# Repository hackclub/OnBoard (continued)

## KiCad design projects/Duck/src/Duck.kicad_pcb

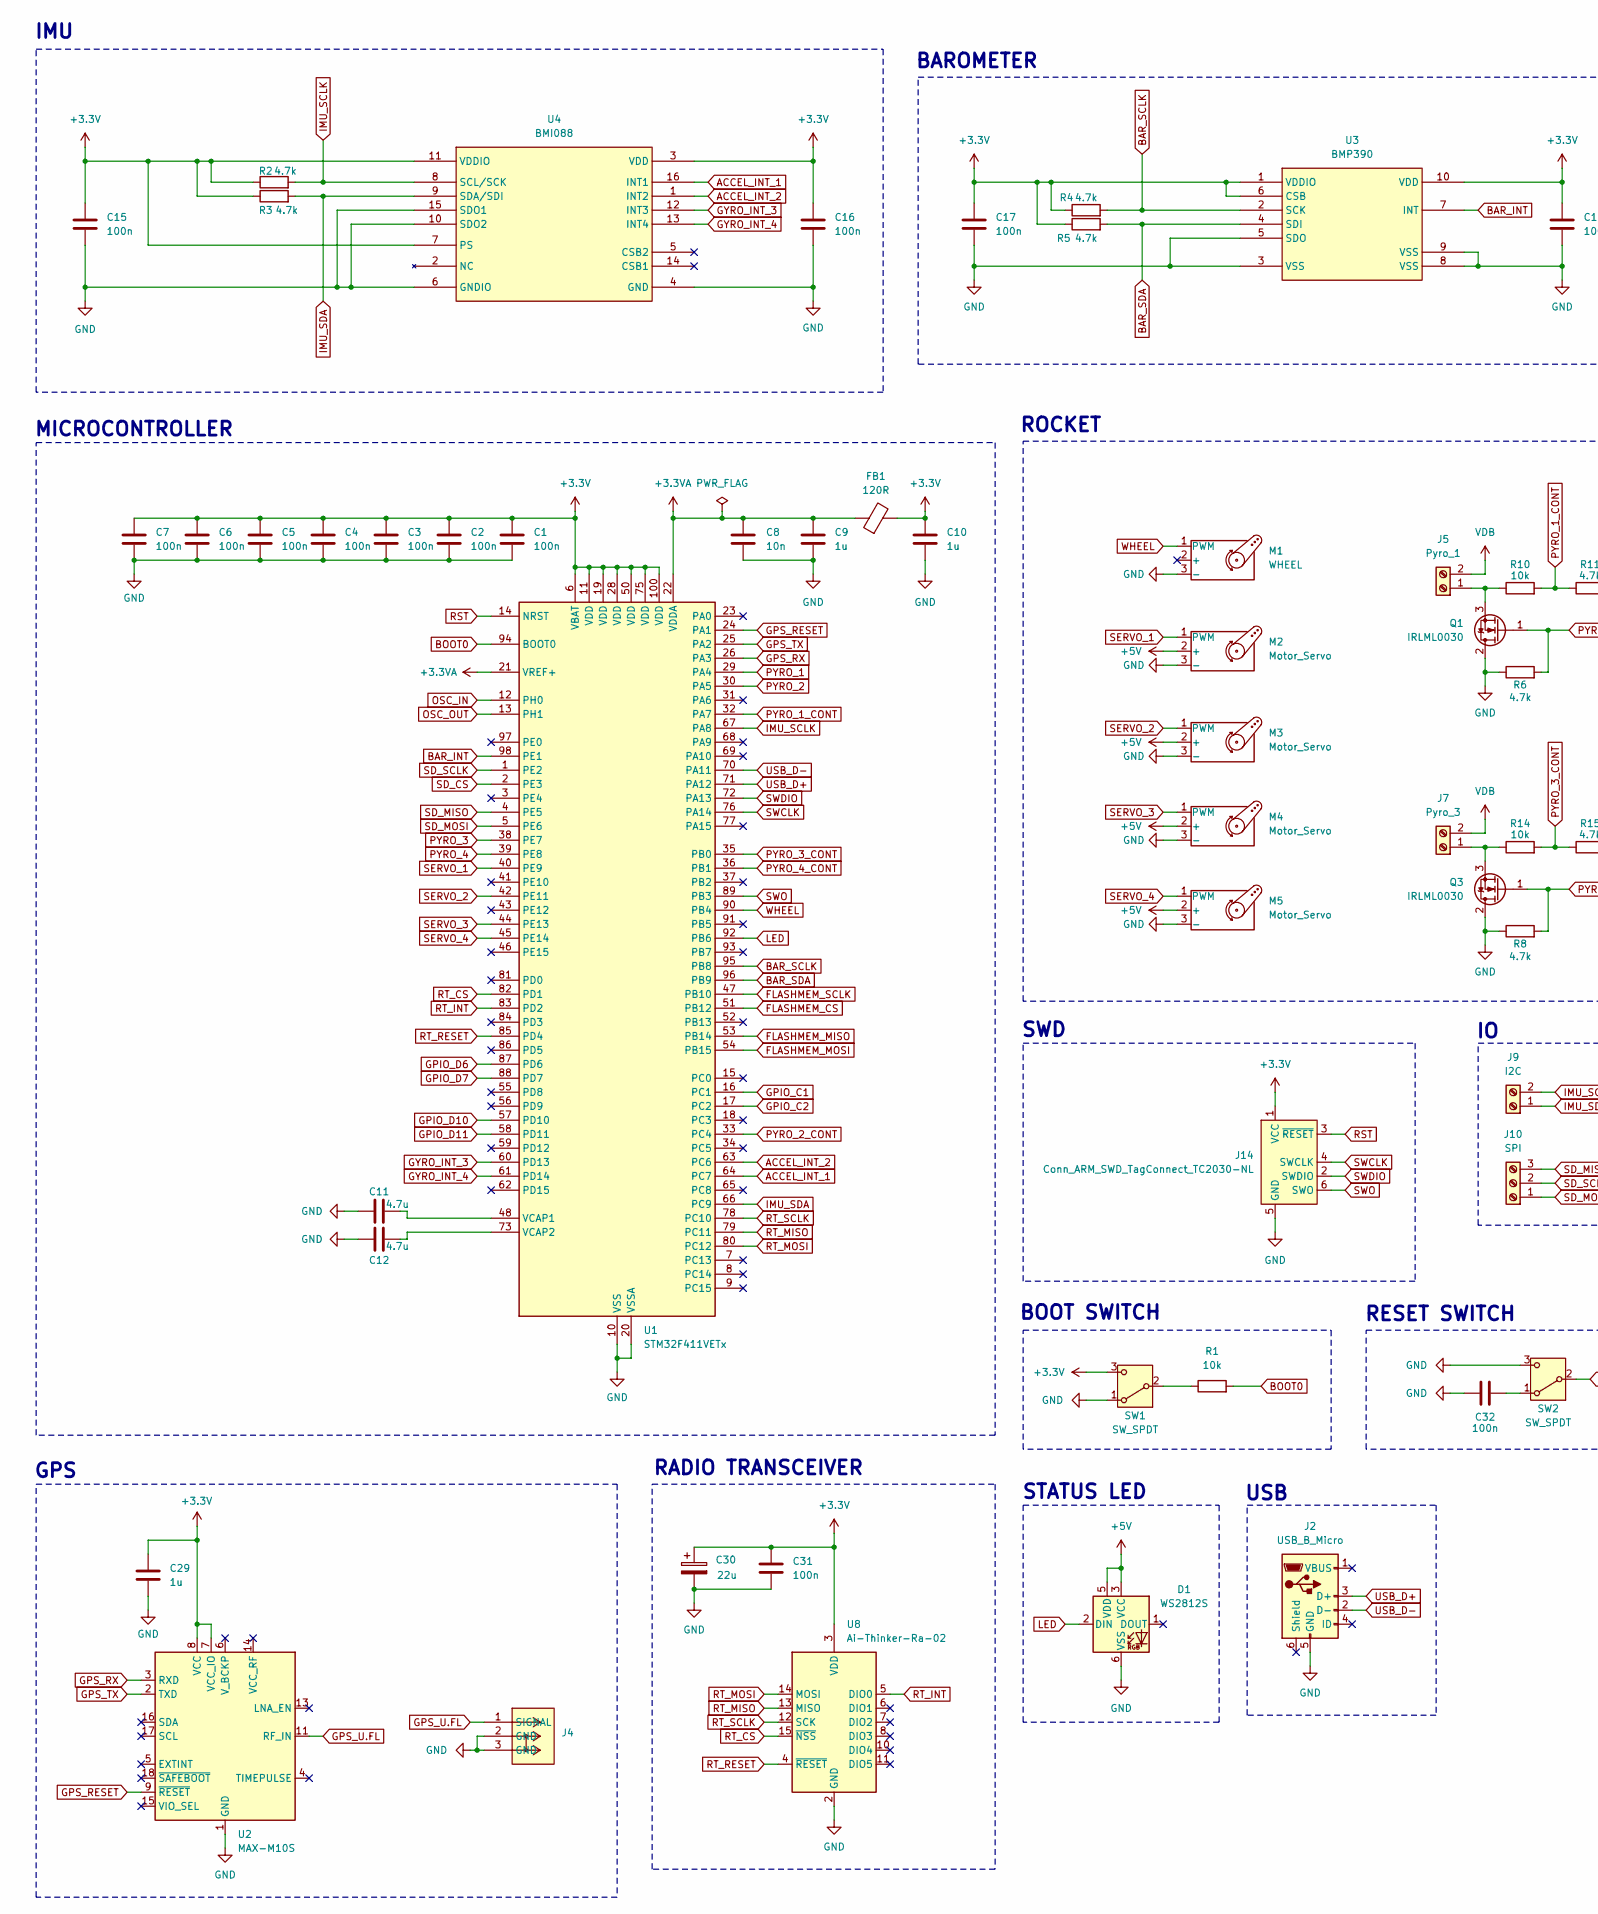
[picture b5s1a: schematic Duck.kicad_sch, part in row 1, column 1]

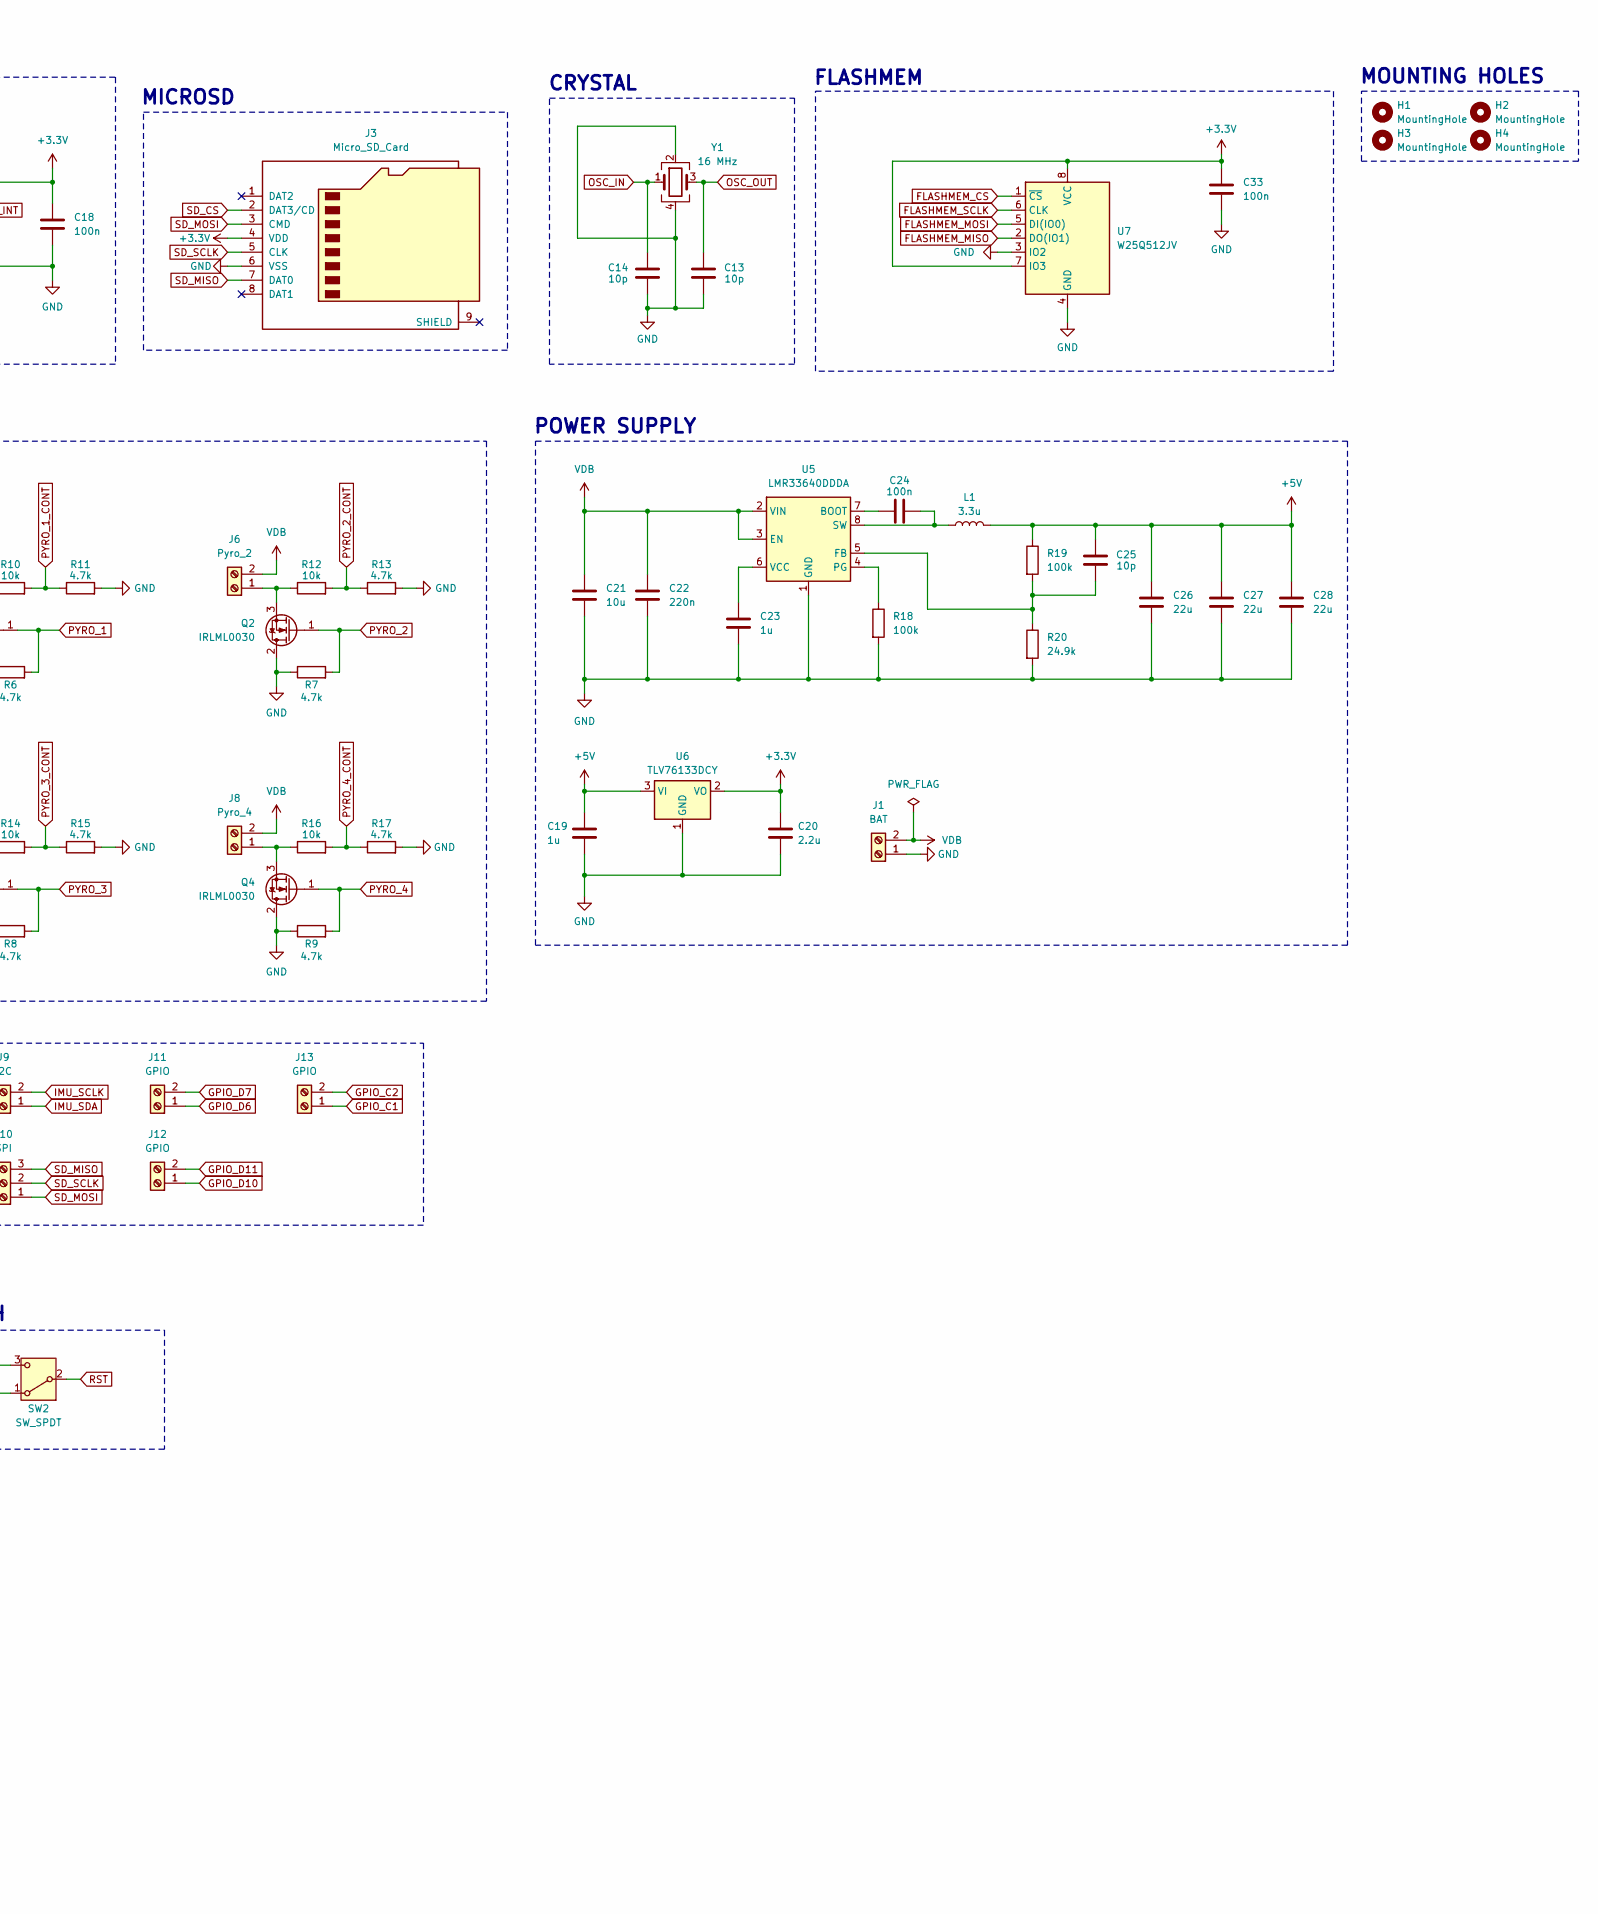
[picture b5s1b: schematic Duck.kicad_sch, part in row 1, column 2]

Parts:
C1, C2, C3, C4, C5, C6, C7, C15, C16, C17, C18, C24, C31, C32, C33: 100n; C_0402_1005Metric
C8: 10n; C_0402_1005Metric
C9, C10, C19, C23, C29: 1u; C_0402_1005Metric
C11, C12: 4.7u; C_0402_1005Metric
C13, C14, C25: 10p; C_0402_1005Metric
C20: 2.2u; C_0402_1005Metric
C21: 10u; C_1206_3216Metric
C22: 220n; C_0603_1608Metric
C26, C27, C28: 22u; C_0603_1608Metric
C30: 22u; CP_Elec_4x5.4
D1: WS2812S; LED_WS2812_PLCC6_5.0x5.0mm_P1.6mm
FB1: 120R; L_0603_1608Metric
H1, H2, H3, H4: MountingHole; MountingHole_2.2mm_M2
J1: BAT; TerminalBlock_Phoenix_MKDS-1,5-2_1x02_P5.00mm_Horizontal
J2: USB_B_Micro; USB_Micro-B_Wuerth_629105150521
J3: Micro_SD_Card; microSD_HC_Wuerth_693072010801
J4: COAX2_U.FL-R-SMT-101_HIR
J5: Pyro_1; TerminalBlock_Phoenix_MKDS-1,5-2_1x02_P5.00mm_Horizontal
J6: Pyro_2; TerminalBlock_Phoenix_MKDS-1,5-2_1x02_P5.00mm_Horizontal
J7: Pyro_3; TerminalBlock_Phoenix_MKDS-1,5-2_1x02_P5.00mm_Horizontal
J8: Pyro_4; TerminalBlock_Phoenix_MKDS-1,5-2_1x02_P5.00mm_Horizontal
J9: I2C; TerminalBlock_Phoenix_MKDS-1,5-2_1x02_P5.00mm_Horizontal
J10: SPI; TerminalBlock_Phoenix_MKDS-1,5-3_1x03_P5.00mm_Horizontal
J11, J12, J13: GPIO; TerminalBlock_Phoenix_MKDS-1,5-2_1x02_P5.00mm_Horizontal
J14: Conn_ARM_SWD_TagConnect_TC2030-NL; Tag-Connect_TC2030-IDC-NL_2x03_P1.27mm_Vertical
L1: 3.3u; L_Coilcraft_XAL4030-XXX
M1: WHEEL; PinHeader_1x03_P2.54mm_Vertical
M2, M3, M4, M5: Motor_Servo; PinHeader_1x03_P2.54mm_Vertical
Q1, Q2, Q3, Q4: IRLML0030; SOT-23
R1, R10, R12, R14, R16: 10k; R_0402_1005Metric
R2, R3, R4, R5, R6, R7, R8, R9, R11, R13, R15, R17: 4.7k; R_0402_1005Metric
R18, R19: 100k; R_0603_1608Metric
R20: 24.9k; R_0603_1608Metric
SW1, SW2: SW_SPDT; SW_SPDT_PCM12
U1: STM32F411VETx; LQFP-100_14x14mm_P0.5mm
U2: MAX-M10S; ublox_MAX
U3: BMP390; 10LGA_2X2X0p75_BOS
U4: BMI088; QFN_BMI085_BOS
U5: LMR33640DDDA; Texas_HSOP-8-1EP_3.9x4.9mm_P1.27mm_ThermalVias
U6: TLV76133DCY; SOT-223-3_TabPin2
U7: W25Q512JV; SON127P600X800X80-9N
U8: Ai-Thinker-Ra-02; Ai-Thinker-Ra-01-LoRa
Y1: 16 MHz; Crystal_SMD_3225-4Pin_3.2x2.5mm

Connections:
+3.3V: C1.1, C2.1, C3.1, C4.1, C5.1, C6.1, C7.1, C10.1, C15.2, C16.2, C17.1, C18.1, C20.1, C29.1, C30.1, C31.2, C33.1, FB1.2, J3.4 (VDD), J14.1 (VCC), R2.1, R3.1, R4.1, R5.1, SW1.3 (C), U1.6 (VBAT), U1.11 (VDD), U1.19 (VDD), U1.28 (VDD), U1.50 (VDD), U1.75 (VDD), U1.100 (VDD), U2.7 (VCC_IO), U2.8 (VCC), U3.1 (VDDIO), U3.6 (CSB), U3.10 (VDD), U4.3 (VDD), U4.7 (PS), U4.11 (VDDIO), U6.2 (VO), U7.7 (IO3), U7.8 (VCC), U8.3 (VDD)
+3.3VA: C8.1, C9.1, FB1.1, U1.21 (VREF+), U1.22 (VDDA)
+5V: C19.1, C25.1, C26.1, C27.1, C28.1, D1.3 (VCC), D1.5 (VDD), L1.2, M2.2 (+), M3.2 (+), M4.2 (+), M5.2 (+), R19.1, U6.3 (VI)
ACCEL_INT_1: U1.64 (PC7), U4.16 (INT1)
ACCEL_INT_2: U1.63 (PC6), U4.1 (INT2)
BAR_INT: U1.98 (PE1), U3.7 (INT)
BAR_SCLK: R4.2, U1.95 (PB8), U3.2 (SCK)
BAR_SDA: R5.2, U1.96 (PB9), U3.4 (SDI)
BOOT0: R1.2, U1.94 (BOOT0)
FLASHMEM_CS: U1.51 (PB12), U7.1 (~CS)
FLASHMEM_MISO: U1.53 (PB14), U7.2 (DO(IO1))
FLASHMEM_MOSI: U1.54 (PB15), U7.5 (DI(IO0))
FLASHMEM_SCLK: U1.47 (PB10), U7.6 (CLK)
GND: C1.2, C2.2, C3.2, C4.2, C5.2, C6.2, C7.2, C8.2, C9.2, C10.2, C11.2, C12.2, C13.2, C14.2, C15.1, C16.1, C17.2, C18.2, C19.2, C20.2, C21.2, C22.2, C23.2, C26.2, C27.2, C28.2, C29.2, C30.2, C31.1, C32.1, C33.2, D1.6 (VSS), J1.1, J2.5 (GND), J3.6 (VSS), J4.2 (GND), J4.3 (GND), J14.5 (GND), M1.3 (-), M2.3 (-), M3.3 (-), M4.3 (-), M5.3 (-), Q1.2 (D), Q2.2 (D), Q3.2 (D), Q4.2 (D), R6.1, R7.1, R8.1, R9.1, R11.2, R13.2, R15.2, R17.2, R18.2, R20.2, SW1.1 (A), SW2.3 (C), U1.10 (VSS), U1.20 (VSSA), U1.27 (VSS), U1.49 (VSS), U1.74 (VSS), U1.99 (VSS), U2.1 (GND), U2.10 (GND), U2.12 (GND), U3.3 (VSS), U3.5 (SDO), U3.8 (VSS), U3.9 (VSS), U4.4 (GND), U4.6 (GNDIO), U4.10 (SDO2), U4.15 (SDO1), U5.1 (GND), U5.9 (GND), U6.1 (GND), U7.3 (IO2), U7.4 (GND), U8.1 (GND), U8.2 (GND), U8.9 (GND), U8.16 (GND), Y1.2, Y1.4
GPIO_C1: J13.1, U1.16 (PC1)
GPIO_C2: J13.2, U1.17 (PC2)
GPIO_D6: J11.1, U1.87 (PD6)
GPIO_D7: J11.2, U1.88 (PD7)
GPIO_D10: J12.1, U1.57 (PD10)
GPIO_D11: J12.2, U1.58 (PD11)
GPS_RESET: U1.24 (PA1), U2.9 (~RESET)
GPS_RX: U1.26 (PA3), U2.3 (RXD)
GPS_TX: U1.25 (PA2), U2.2 (TXD)
GPS_U.FL: J4.1 (SIGNAL), U2.11 (RF_IN)
GYRO_INT_3: U1.60 (PD13), U4.12 (INT3)
GYRO_INT_4: U1.61 (PD14), U4.13 (INT4)
IMU_SCLK: J9.2, R2.2, U1.67 (PA8), U4.8 (SCL/SCK)
IMU_SDA: J9.1, R3.2, U1.66 (PC9), U4.9 (SDA/SDI)
LED: D1.2 (DIN), U1.92 (PB6)
unnamed: J5.1, Q1.3 (S), R10.1
unnamed: J6.1, Q2.3 (S), R12.1
unnamed: J7.1, Q3.3 (S), R14.1
unnamed: J8.1, Q4.3 (S), R16.1
unnamed: R1.1, SW1.2 (B)
unnamed: C32.2, SW2.1 (A)
unnamed: C11.1, U1.48 (VCAP1)
unnamed: C12.1, U1.73 (VCAP2)
unnamed: C24.1, U5.7 (BOOT)
unnamed: C25.2, R19.2, R20.1, U5.5 (FB)
unnamed: R18.1, U5.4 (PG)
unnamed: C24.2, L1.1, U5.8 (SW)
unnamed: C23.1, U5.6 (VCC)
OSC_IN: C14.1, U1.12 (PH0), Y1.1
OSC_OUT: C13.1, U1.13 (PH1), Y1.3
PYRO_1: Q1.1 (G), R6.2, U1.29 (PA4)
PYRO_1_CONT: R10.2, R11.1, U1.32 (PA7)
PYRO_2: Q2.1 (G), R7.2, U1.30 (PA5)
PYRO_2_CONT: R12.2, R13.1, U1.33 (PC4)
PYRO_3: Q3.1 (G), R8.2, U1.38 (PE7)
PYRO_3_CONT: R14.2, R15.1, U1.35 (PB0)
PYRO_4: Q4.1 (G), R9.2, U1.39 (PE8)
PYRO_4_CONT: R16.2, R17.1, U1.36 (PB1)
RST: J14.3 (~RESET), SW2.2 (B), U1.14 (NRST)
RT_CS: U1.82 (PD1), U8.15 (~NSS)
RT_INT: U1.83 (PD2), U8.5 (DIO0)
RT_MISO: U1.79 (PC11), U8.13 (MISO)
RT_MOSI: U1.80 (PC12), U8.14 (MOSI)
RT_RESET: U1.85 (PD4), U8.4 (~RESET)
RT_SCLK: U1.78 (PC10), U8.12 (SCK)
SD_CS: J3.2 (DAT3/CD), U1.2 (PE3)
SD_MISO: J3.7 (DAT0), J10.3, U1.4 (PE5)
SD_MOSI: J3.3 (CMD), J10.1, U1.5 (PE6)
SD_SCLK: J3.5 (CLK), J10.2, U1.1 (PE2)
SERVO_1: M2.1 (PWM), U1.40 (PE9)
SERVO_2: M3.1 (PWM), U1.42 (PE11)
SERVO_3: M4.1 (PWM), U1.44 (PE13)
SERVO_4: M5.1 (PWM), U1.45 (PE14)
SWCLK: J14.4 (SWCLK), U1.76 (PA14)
SWDIO: J14.2 (SWDIO), U1.72 (PA13)
SWO: J14.6 (SWO), U1.89 (PB3)
USB_D+: J2.3 (D+), U1.71 (PA12)
USB_D-: J2.2 (D-), U1.70 (PA11)
VDB: C21.1, C22.1, J1.2, J5.2, J6.2, J7.2, J8.2, U5.2 (VIN), U5.3 (EN)
WHEEL: M1.1 (PWM), U1.90 (PB4)

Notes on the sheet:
RESET SWITCH
MICROCONTROLLER
POWER SUPPLY
RADIO TRANSCEIVER
BAROMETER
SWD
ROCKET
FLASHMEM
GPS
USB
BOOT SWITCH
MICROSD
STATUS LED
CRYSTAL
IMU
MOUNTING HOLES

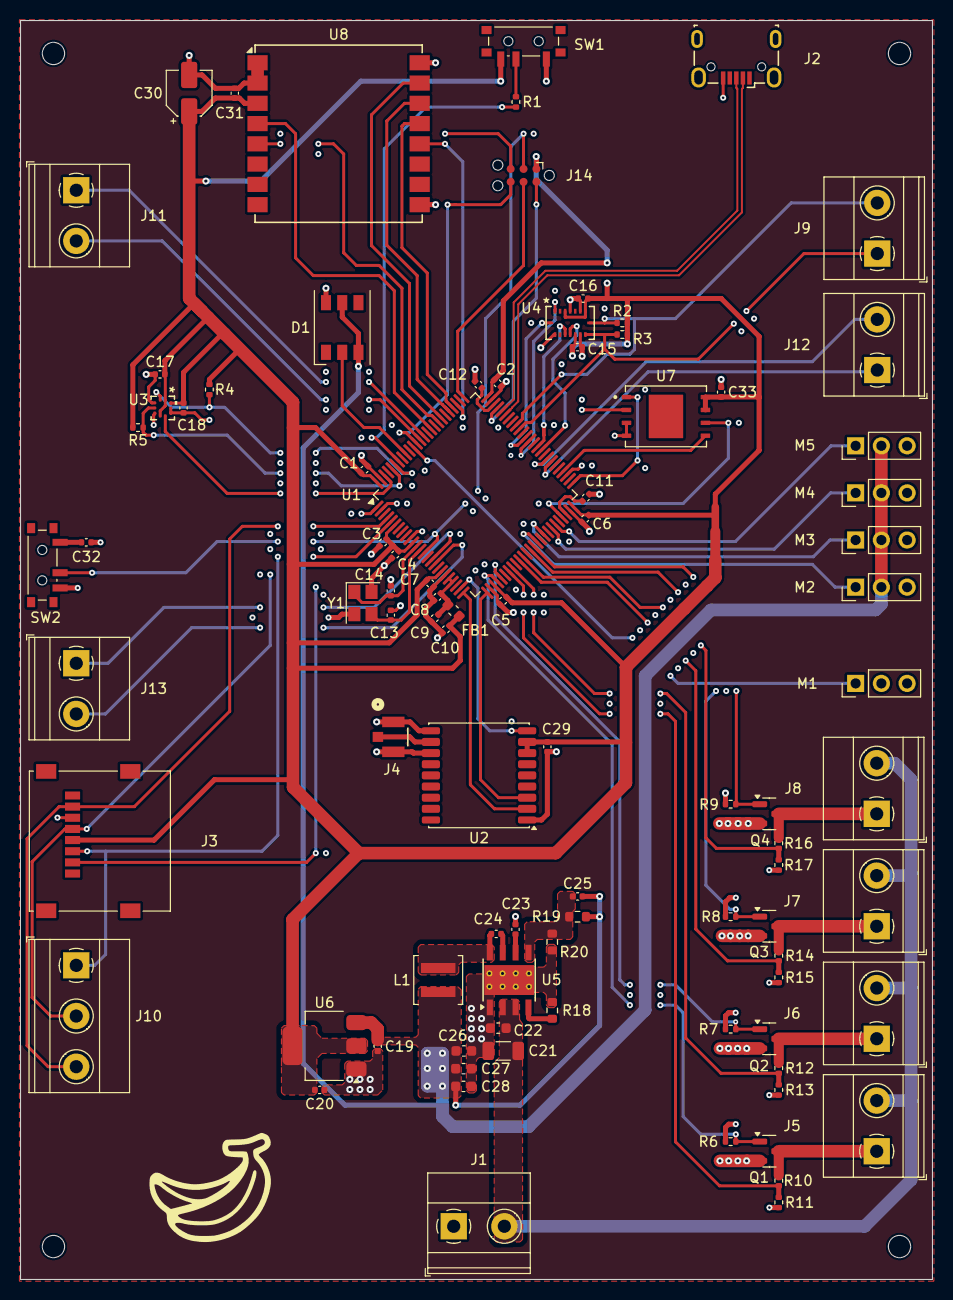
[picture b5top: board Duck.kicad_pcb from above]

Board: 4 copper layers, 90.0 x 124.2 mm, 94 parts (0 on the bottom side), 74 nets.

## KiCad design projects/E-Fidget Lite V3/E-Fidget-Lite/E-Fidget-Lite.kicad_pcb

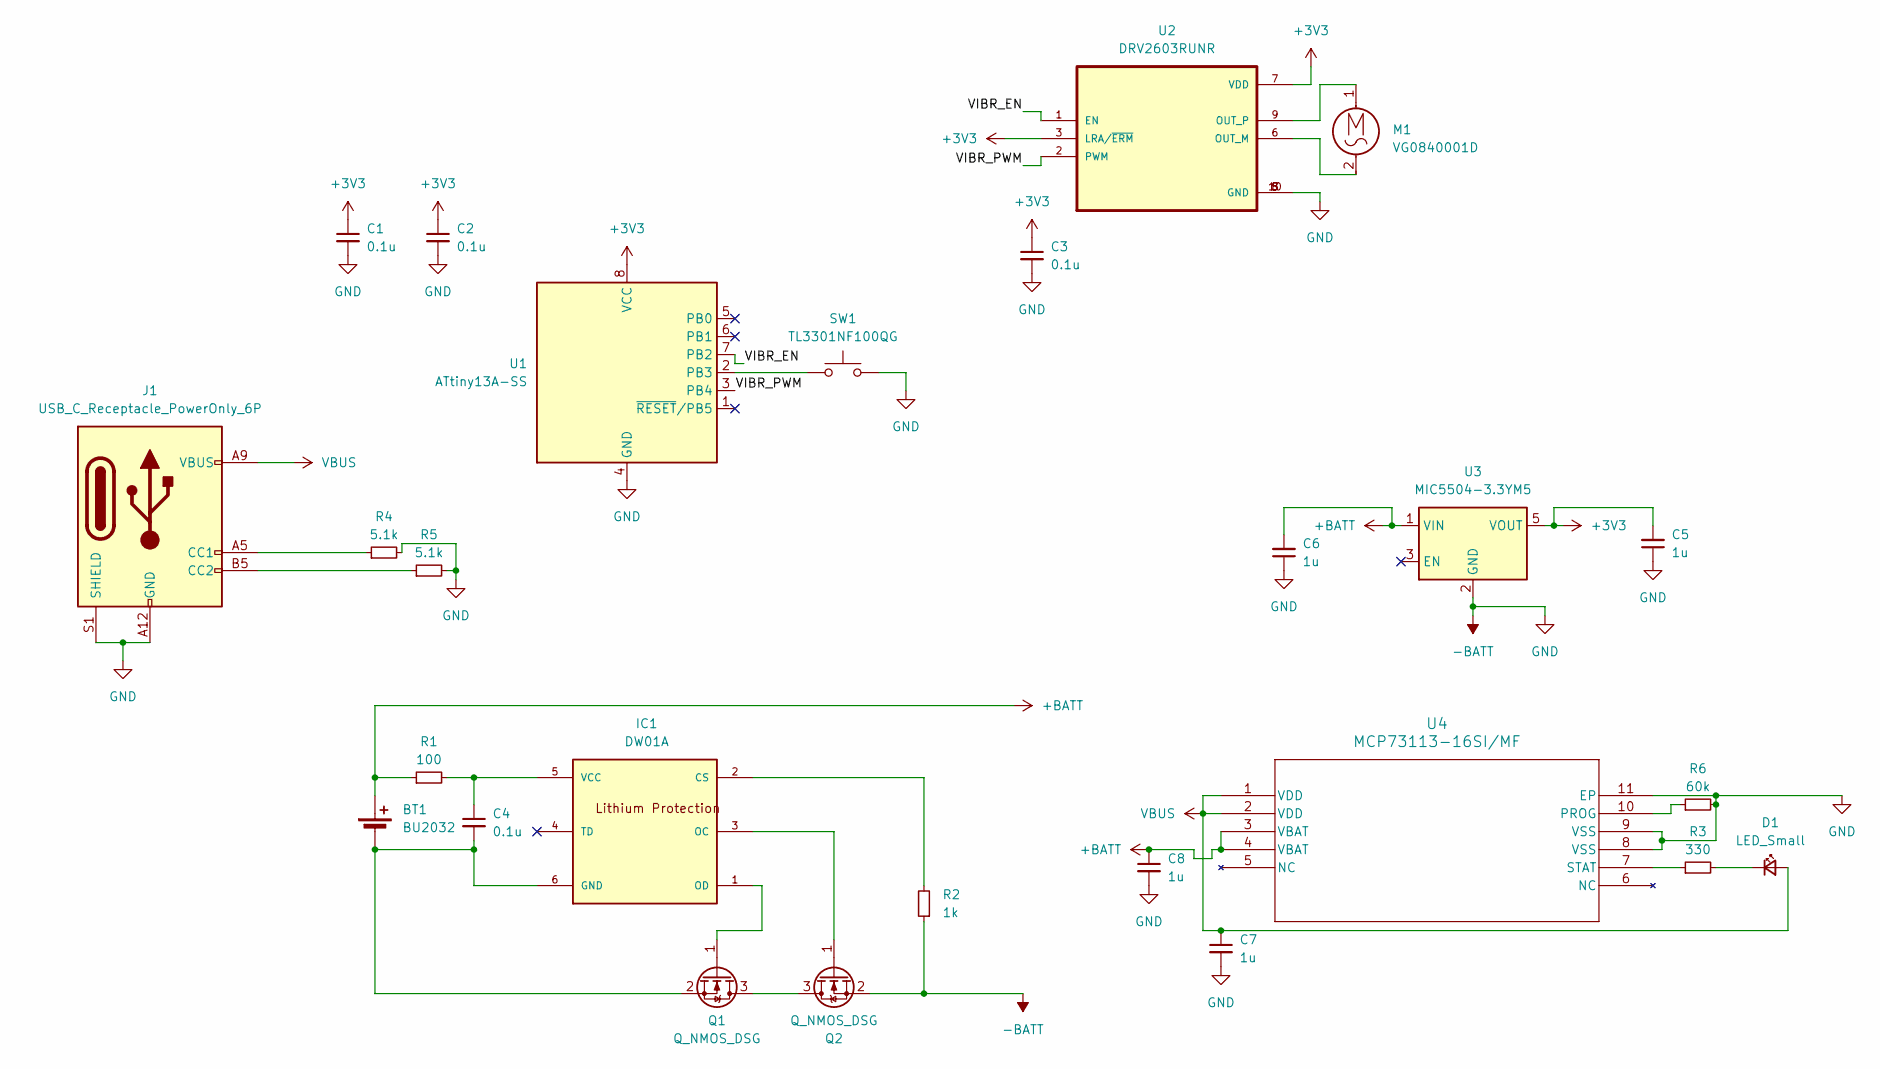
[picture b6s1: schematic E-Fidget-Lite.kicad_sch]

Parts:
BT1: BU2032; BAT_BU2032-1-HD-G
C1, C2, C3, C4: 0.1u; C_0402_1005Metric
C5, C6, C7, C8: 1u; C_0402_1005Metric
D1: LED_Small; LED_0603_1608Metric
IC1: DW01A; SOT-23-6; MPN DW01A; LCSC C351410
J1: USB_C_Receptacle_PowerOnly_6P; USB_C_Receptacle_GCT_USB4135-GF-A_6P_TopMnt_Horizontal
M1: VG0840001D; MotorPads
Q1, Q2: Q_NMOS_DSG; SOT-23-3
R1: 100; R_0402_1005Metric
R2: 1k; R_0402_1005Metric
R3: 330; R_0402_1005Metric
R4, R5: 5.1k; R_0402_1005Metric
R6: 60k; R_0603_1608Metric
SW1: TL3301NF100QG; SW_Push_1P1T_NO_6x6mm_H9.5mm_LongPads
U1: ATtiny13A-SS; SOIC-8_3.9x4.9mm_P1.27mm; PartNumber ATtiny13A-SS
U2: DRV2603RUNR; QFN50P200X200X80-10N; PARTREV C
U3: MIC5504-3.3YM5; SOT-23-5
U4: MCP73113-16SI/MF; DFN10_3x3MC_MCH

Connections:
+3V3: C1.1, C2.1, C3.1, C5.2, U1.8 (VCC), U2.3 (LRA/~ERM), U2.7 (VDD), U3.5 (VOUT)
+BATT: BT1.1 (+), C6.2, C8.1, R1.1, U3.1 (VIN), U4.3 (VBAT), U4.4 (VBAT)
-BATT: C1.2, C2.2, C3.2, C5.1, C6.1, C7.2, C8.2, J1.A12 (GND), J1.B12 (GND), J1.S1 (SHIELD), Q2.2 (S), R2.1, R4.2, R5.2, R6.2, SW1.2, U1.4 (GND), U2.5 (GND), U2.8 (GND), U2.10 (GND), U3.2 (GND), U4.8 (VSS), U4.9 (VSS), U4.11 (EP)
/VIBR_EN: U1.7 (PB2), U2.1 (EN)
/VIBR_PWM: U1.3 (PB4), U2.2 (PWM)
unnamed: BT1.2 (-), C4.2, IC1.6 (GND), Q1.2 (S)
unnamed: D1.1 (K), R3.2
unnamed: IC1.2 (CS), R2.2
unnamed: IC1.3 (OC), Q2.1 (G)
unnamed: IC1.1 (OD), Q1.1 (G)
unnamed: C4.1, IC1.5 (VCC), R1.2
unnamed: J1.A5 (CC1), R4.1
unnamed: J1.B5 (CC2), R5.1
unnamed: Q1.3 (D), Q2.3 (D)
unnamed: SW1.1, U1.2 (PB3)
unnamed: M1.2, U2.6 (OUT_M)
unnamed: M1.1, U2.9 (OUT_P)
unnamed: R6.1, U4.10 (PROG)
unnamed: R3.1, U4.7 (STAT)
VBUS: C7.1, D1.2 (A), J1.A9 (VBUS), J1.B9 (VBUS), U4.1 (VDD), U4.2 (VDD)

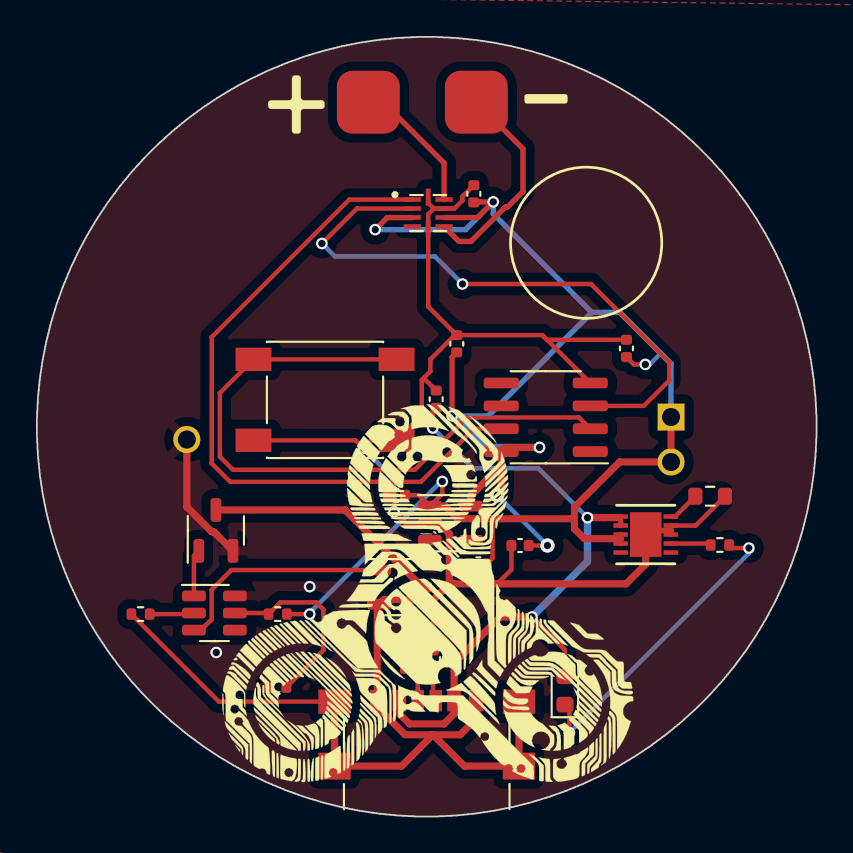
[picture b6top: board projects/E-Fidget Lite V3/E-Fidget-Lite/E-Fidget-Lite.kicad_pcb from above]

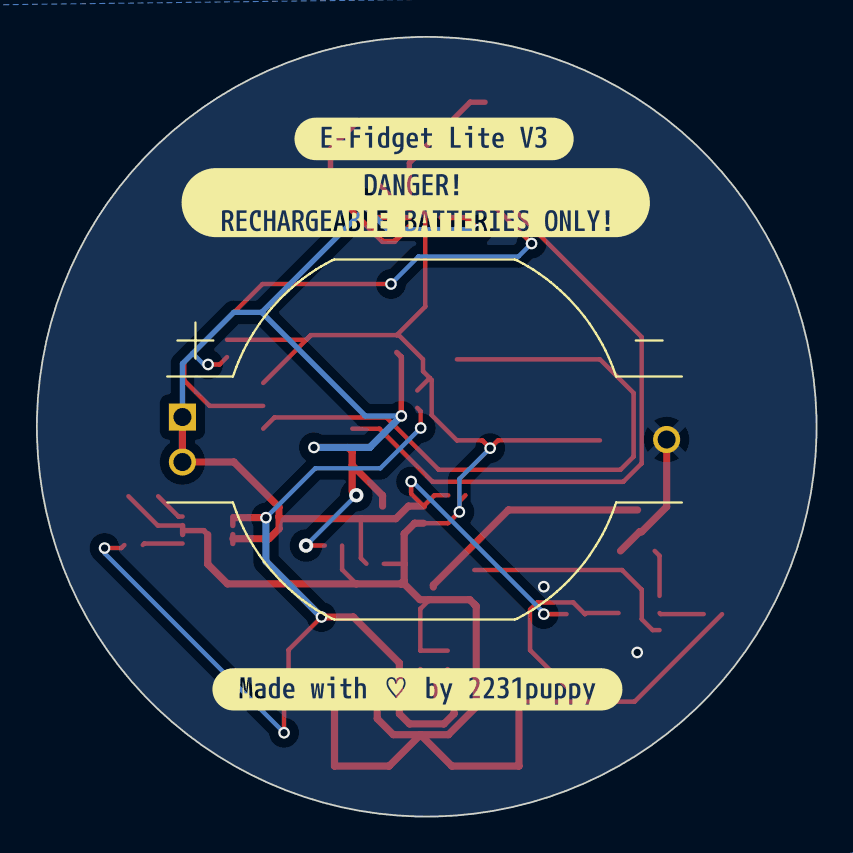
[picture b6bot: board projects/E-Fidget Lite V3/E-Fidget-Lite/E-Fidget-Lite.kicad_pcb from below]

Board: 2 copper layers, 43.3 x 43.3 mm, 29 parts (4 on the bottom side), 20 nets.

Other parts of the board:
kibuzzard-64E02DE0: G***; kibuzzard-64E02DE0
kibuzzard-650B44AE: G***; kibuzzard-650B44AE
kibuzzard-6472B1FB: G***; kibuzzard-6472B1FB

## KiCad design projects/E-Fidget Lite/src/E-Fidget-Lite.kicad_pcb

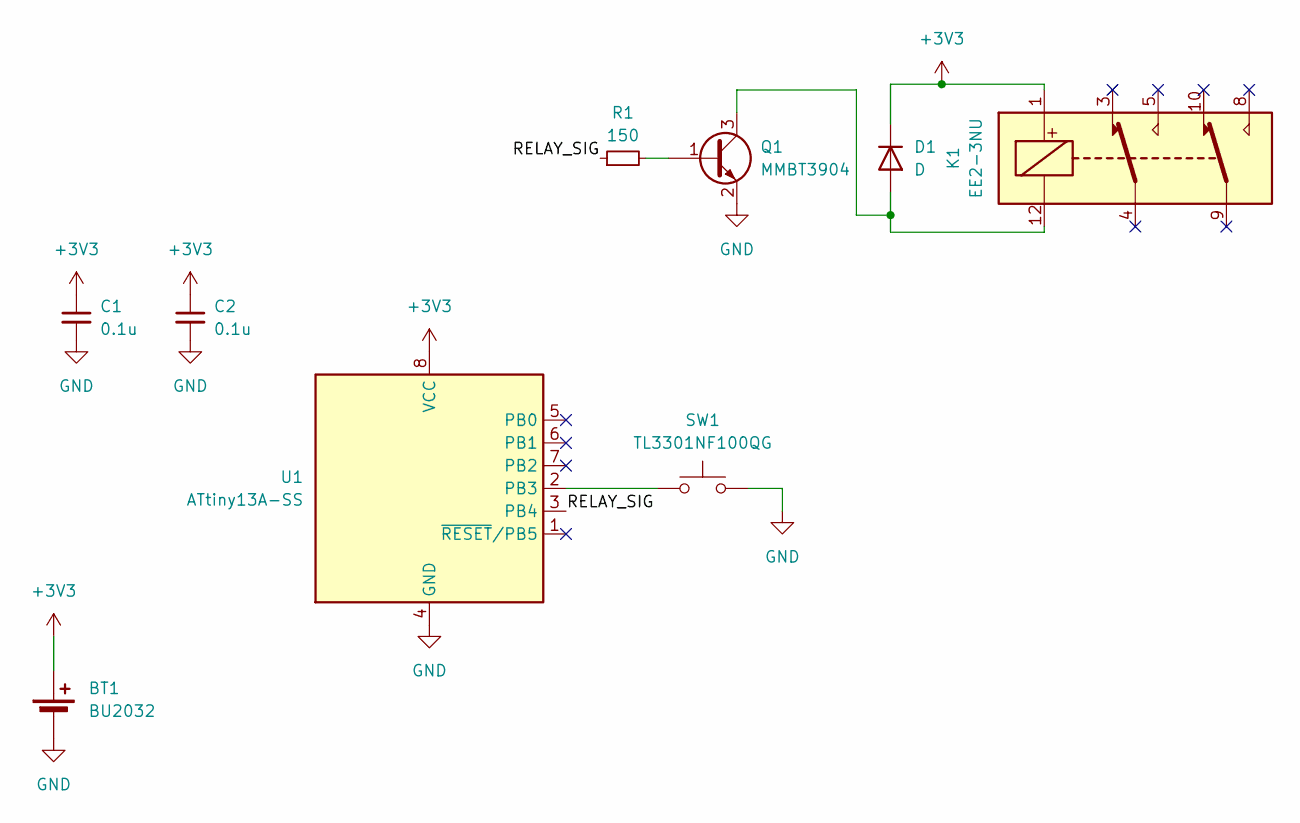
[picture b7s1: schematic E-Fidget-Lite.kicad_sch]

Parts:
BT1: BU2032; BAT_BU2032-1-HD-G
C1, C2: 0.1u; C_0402_1005Metric
D1: D; D_SOD-123
K1: EE2-3NU; Relay_DPDT_Kemet_EC2
Q1: MMBT3904; SOT-23
R1: 150; R_0402_1005Metric
SW1: TL3301NF100QG; SW_Push_1P1T_NO_6x6mm_H9.5mm
U1: ATtiny13A-SS; SOIC-8_3.9x4.9mm_P1.27mm

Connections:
+3V3: BT1.1 (+), C1.1, C2.1, D1.1 (K), K1.1, U1.8 (VCC)
/RELAY_SIG: R1.1, U1.3 (PB4)
GND: BT1.2 (-), C1.2, C2.2, Q1.2 (E), SW1.2, U1.4 (GND)
unnamed: D1.2 (A), K1.12, Q1.3 (C)
unnamed: Q1.1 (B), R1.2
unnamed: SW1.1, U1.2 (PB3)

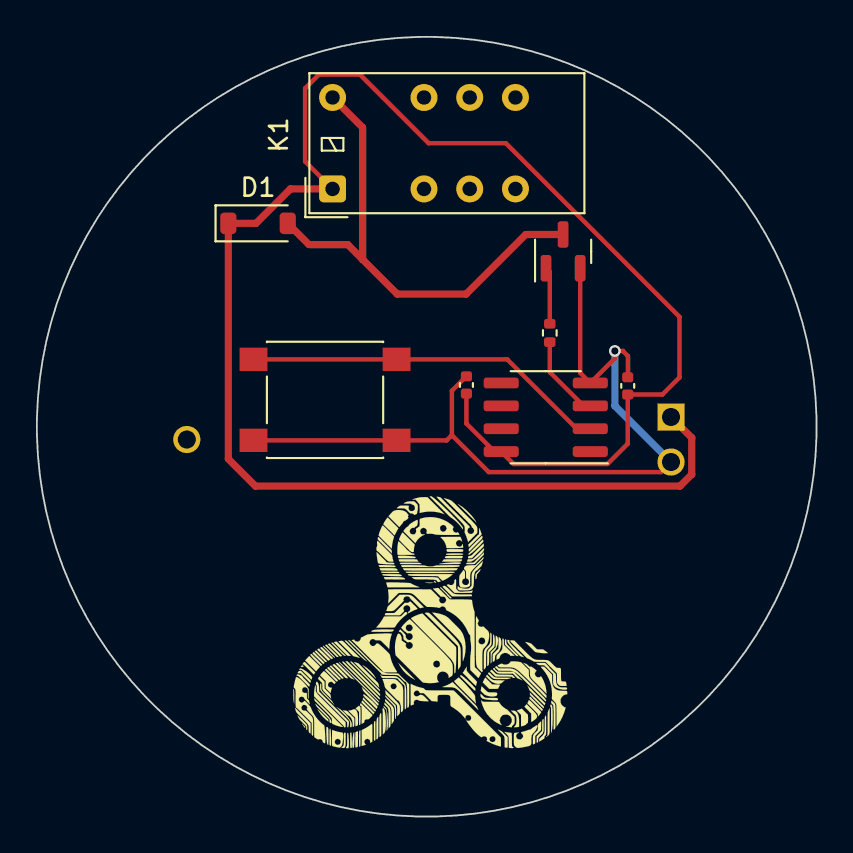
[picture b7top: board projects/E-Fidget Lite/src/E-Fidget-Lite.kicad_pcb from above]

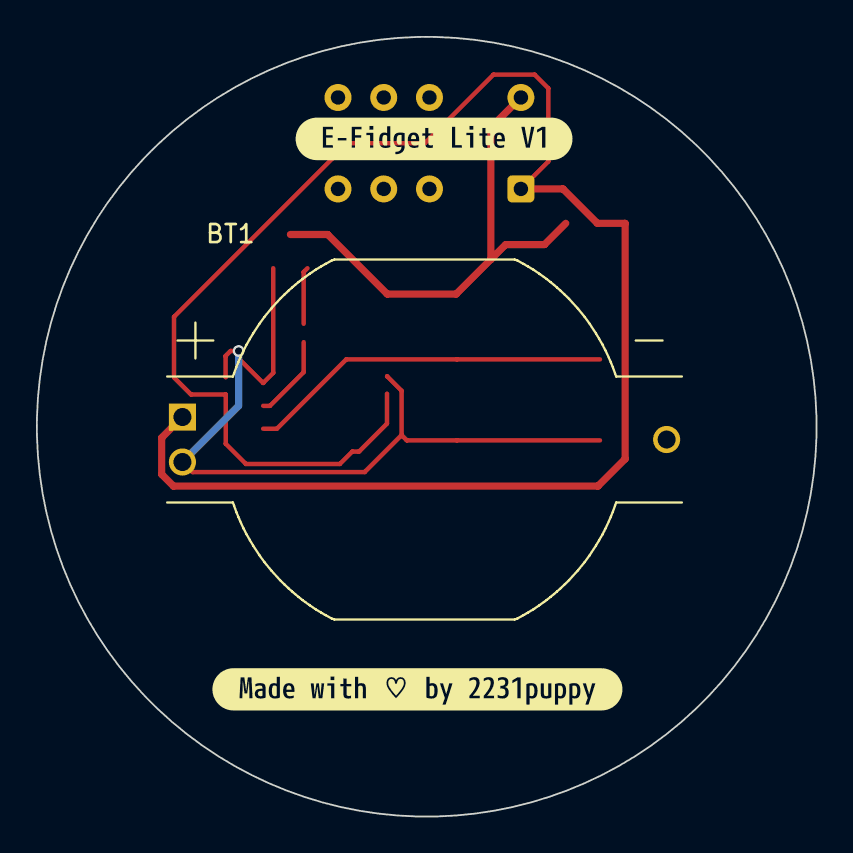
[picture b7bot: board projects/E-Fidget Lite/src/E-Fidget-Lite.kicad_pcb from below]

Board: 2 copper layers, 43.3 x 43.3 mm, 11 parts (3 on the bottom side), 6 nets.

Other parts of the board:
kibuzzard-6472B1FB: G***; kibuzzard-6472B1FB
kibuzzard-6472B22C: G***; kibuzzard-6472B22C
